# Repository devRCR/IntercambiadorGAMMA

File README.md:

# IntercambiadorGAMMA
Distributed control system for a Gamma heat exchanger using microcontrollers. Includes a Master Node for user input and two Slave Nodes for spindle and wheel control. Nodes communicate via serial protocol with modular Arduino-based C++ code for synchronized and reliable automation.

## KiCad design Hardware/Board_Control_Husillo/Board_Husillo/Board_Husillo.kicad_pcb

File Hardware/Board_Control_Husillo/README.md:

# Husillo Board – Intercambiador Gamma

Este documento describe la placa electrónica utilizada para el control del **módulo de husillo** en el sistema de automatización del intercambiador Gamma, desarrollado por el **Laboratorio de Desarrollo Electrónico – IPEN**.

## 📷 Diagrama de la Placa

## 🔧 Descripción Técnica

La placa está diseñada para:

- Controlar un **motor paso a paso** mediante señales `STEP` y `DIR`.
- Alimentar y conmutar un **relé de captura** para el sistema Marinelli.
- Leer múltiples **sensores de posición** (ópticos o magnéticos).
- Integrar un **buzzer** para notificación acústica.
- Interfaz directa con **Arduino Mega 2560** a través de conectores macho/hembra.
- Soporte de comunicación serial (TTL) para control distribuido.

## 🧩 Interfaces

| Señal          | Función                          |
|----------------|----------------------------------|
| `M_EN`         | Habilitación de motor            |
| `M_STEP`       | Pulso de avance                  |
| `M_DIR`        | Dirección de movimiento          |
| `RELAY`        | Activación del sistema Marinelli |
| `SENS_POS1-3`  | Sensores de posición del husillo |
| `SENS_MARx`    | Sensores de estado de Marinelli  |
| `BUZZER`       | Alarma sonora                    |
| `LCD`          | Salida para pantalla LCD 16x2    |

## 🛠️ Fabricación

- PCB de doble cara
- Conectores tipo Molex o bornes atornillables
- Compatible con montaje en riel DIN o chasis metálico

## 📄 Licencia

Este diseño se distribuye bajo **Creative Commons Atribución-NoComercial 4.0 Internacional (CC BY-NC 4.0)**. Su uso y modificación están permitidos únicamente para fines no comerciales, con la debida atribución a los autores.

## 👤 Autores

- O. Baltuano  
- R. Chan  
**Laboratorio de Desarrollo Electrónico – IPEN**

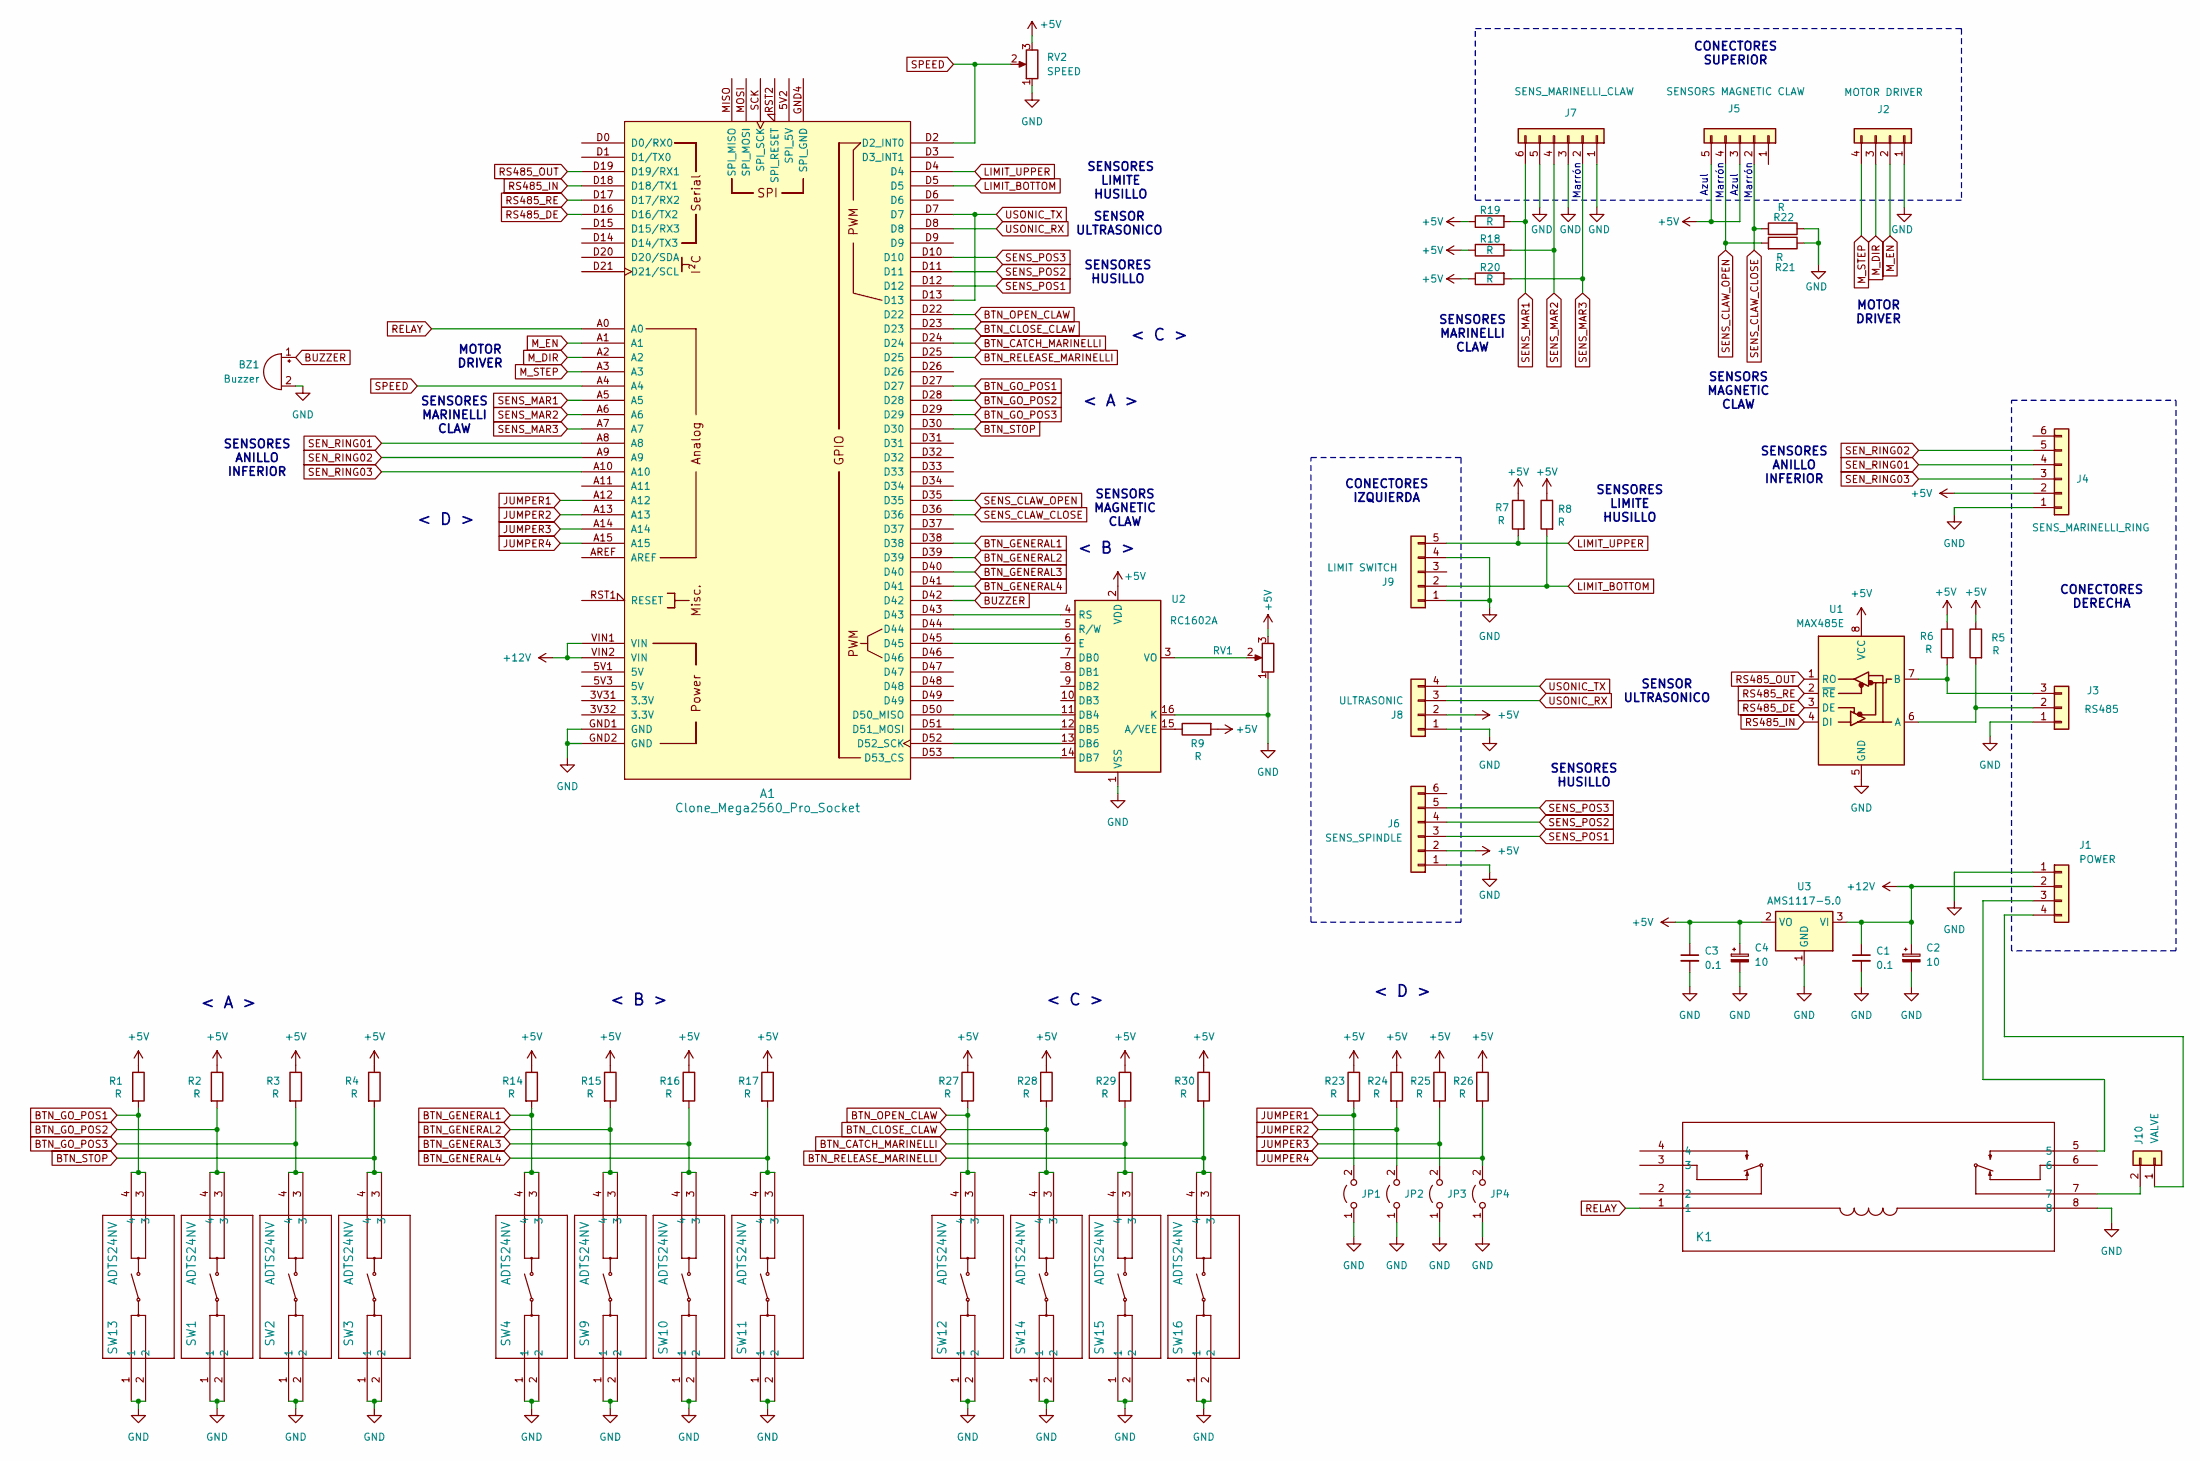
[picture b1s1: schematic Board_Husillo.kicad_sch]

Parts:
A1: Clone_Mega2560_Pro_Socket
BZ1: Buzzer; Buzzer_12x9.5RM7.6
C1, C3: 0.1; C_0805_2012Metric
C2, C4: 10; CP_Radial_D5.0mm_P2.50mm
J1: POWER; Molex_KK-396_5273-04A_1x04_P3.96mm_Vertical
J2: MOTOR DRIVER; PinHeader_1x04_P2.54mm_Vertical
J3: RS485; PinHeader_1x03_P2.54mm_Vertical
J4: SENS_MARINELLI_RING; PinHeader_1x06_P2.54mm_Vertical
J5: SENSORS MAGNETIC CLAW; PinHeader_1x05_P2.54mm_Vertical
J6: SENS_SPINDLE; PinHeader_1x06_P2.54mm_Vertical
J7: SENS_MARINELLI_CLAW; PinHeader_1x06_P2.54mm_Vertical
J8: ULTRASONIC; PinHeader_1x04_P2.54mm_Vertical
J9: LIMIT SWITCH; PinHeader_1x05_P2.54mm_Vertical
J10: VALVE; Molex_KK-396_A-41791-0002_1x02_P3.96mm_Vertical
JP1, JP2, JP3, JP4: Jumper_2_Open; PinHeader_1x02_P2.54mm_Vertical
K1: HRS2H-S DC12V; HRS2H-S DC9V_MTC
R1, R2, R3, R4, R9, R14, R15, R16, R17, R27, R28, R29, R30: R; R_Axial_DIN0207_L6.3mm_D2.5mm_P7.62mm_Horizontal
R5, R6, R7, R8, R18, R19, R20, R21, R22, R23, R24, R25, R26: R; R_0805_2012Metric
RV1: CONTRASTE; Potentiometer_ACP_CA9-V10_Vertical
RV2: SPEED; Potentiometer_ACP_CA9-V10_Vertical
SW1, SW2, SW3, SW4, SW9, SW10, SW11, SW12, SW13, SW14, SW15, SW16: ADTS24NV; ADTS24&asterisk_V_APM
U1: MAX485E; SOIC-8_5.23x5.23mm_P1.27mm
U2: RC1602A; WC1602A
U3: AMS1117-5.0; SOT-223-3_TabPin2

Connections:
+5V: C3.1, C4.1, J4.2, J5.3, J5.5, J6.2, J8.2, R1.1, R2.1, R3.1, R4.1, R5.1, R6.1, R7.1, R8.1, R9.2, R14.1, R15.1, R16.1, R17.1, R18.1, R19.1, R20.1, R23.1, R24.1, R25.1, R26.1, R27.1, R28.1, R29.1, R30.1, RV1.3, RV2.3, U1.8 (VCC), U2.2 (VDD), U3.2 (VO)
+12V: A1.VIN1 (VIN), A1.VIN2 (VIN), C1.1, C2.1, J1.2, U3.3 (VI)
BTN_CATCH_MARINELLI: A1.D24, R29.2, SW15.3, SW15.4
BTN_CLOSE_CLAW: A1.D23, R28.2, SW14.3, SW14.4
BTN_GENERAL1: A1.D38, R14.2, SW4.3, SW4.4
BTN_GENERAL2: A1.D39, R15.2, SW9.3, SW9.4
BTN_GENERAL3: A1.D40, R16.2, SW10.3, SW10.4
BTN_GENERAL4: A1.D41, R17.2, SW11.3, SW11.4
BTN_GO_POS1: A1.D27, R1.2, SW13.3, SW13.4
BTN_GO_POS2: A1.D28, R2.2, SW1.3, SW1.4
BTN_GO_POS3: A1.D29, R3.2, SW2.3, SW2.4
BTN_OPEN_CLAW: A1.D22, R27.2, SW12.3, SW12.4
BTN_RELEASE_MARINELLI: A1.D25, R30.2, SW16.3, SW16.4
BTN_STOP: A1.D30, R4.2, SW3.3, SW3.4
BUZZER: A1.D42, BZ1.1 (+)
GND: A1.GND1 (GND), A1.GND2 (GND), BZ1.2 (-), C1.2, C2.2, C3.2, C4.2, J1.1, J2.1, J3.1, J4.1, J6.1, J7.1, J7.3, J7.5, J8.1, J9.1, J9.4, JP1.1 (A), JP2.1 (A), JP3.1 (A), JP4.1 (A), K1.8, R21.1, R22.1, RV1.1, RV2.1, SW1.1, SW1.2, SW2.1, SW2.2, SW3.1, SW3.2, SW4.1, SW4.2, SW9.1, SW9.2, SW10.1, SW10.2, SW11.1, SW11.2, SW12.1, SW12.2, SW13.1, SW13.2, SW14.1, SW14.2, SW15.1, SW15.2, SW16.1, SW16.2, U1.5 (GND), U2.1 (VSS), U2.16 (K), U3.1 (GND)
JUMPER1: A1.A12, JP1.2 (B), R23.2
JUMPER2: A1.A13, JP2.2 (B), R24.2
JUMPER3: A1.A14, JP3.2 (B), R25.2
JUMPER4: A1.A15, JP4.2 (B), R26.2
LIMIT_BOTTOM: A1.D5, J9.2, R8.2
LIMIT_UPPER: A1.D4, J9.5, R7.2
M_DIR: A1.A2, J2.3
M_EN: A1.A1, J2.2
M_STEP: A1.A3, J2.4
unnamed: A1.A4, A1.D2 (D2_INT0), RV2.2
unnamed: A1.D50 (D50_MISO), U2.11 (DB4)
unnamed: A1.D51 (D51_MOSI), U2.12 (DB5)
unnamed: A1.D52 (D52_SCK), U2.13 (DB6)
unnamed: A1.D53 (D53_CS), U2.14 (DB7)
unnamed: J1.3, K1.5
unnamed: J1.4, J10.1
unnamed: J3.2, R5.2, U1.6 (A)
unnamed: J3.3, R6.2, U1.7 (B)
unnamed: J10.2, K1.7
unnamed: R9.1, U2.15 (A/VEE)
unnamed: A1.D45, U2.6 (E)
unnamed: A1.D43, U2.4 (RS)
unnamed: A1.D44, U2.5 (R/W)
unnamed: RV1.2, U2.3 (VO)
RELAY: A1.A0, K1.1
RS485_DE: A1.D16 (D16/TX2), U1.3 (DE)
RS485_IN: A1.D18 (D18/TX1), U1.4 (DI)
RS485_OUT: A1.D19 (D19/RX1), U1.1 (RO)
RS485_RE: A1.D17 (D17/RX2), U1.2 (~RE)
SENS_CLAW_CLOSE: A1.D36, J5.2, R22.2
SENS_CLAW_OPEN: A1.D35, J5.4, R21.2
SENS_MAR1: A1.A5, J7.6, R19.2
SENS_MAR2: A1.A6, J7.4, R18.2
SENS_MAR3: A1.A7, J7.2, R20.2
SENS_POS1: A1.D12, J6.3
SENS_POS2: A1.D11, J6.4
SENS_POS3: A1.D10, J6.5
SEN_RING01: A1.A8, J4.4
SEN_RING02: A1.A9, J4.5
SEN_RING03: A1.A10, J4.3
USONIC_RX: A1.D8, J8.3
USONIC_TX: A1.D7, A1.D13, J8.4

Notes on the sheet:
Marrón
SENSORS MAGNETIC CLAW
< D >
SENSORES LIMITE HUSILLO
CONECTORES SUPERIOR
SENSORES MARINELLI CLAW
CONECTORES DERECHA
CONECTORES IZQUIERDA
MOTOR DRIVER
< A >
< C >
Azul
SENSOR ULTRASONICO
SENSORES HUSILLO
SENSORES ANILLO INFERIOR
< B >

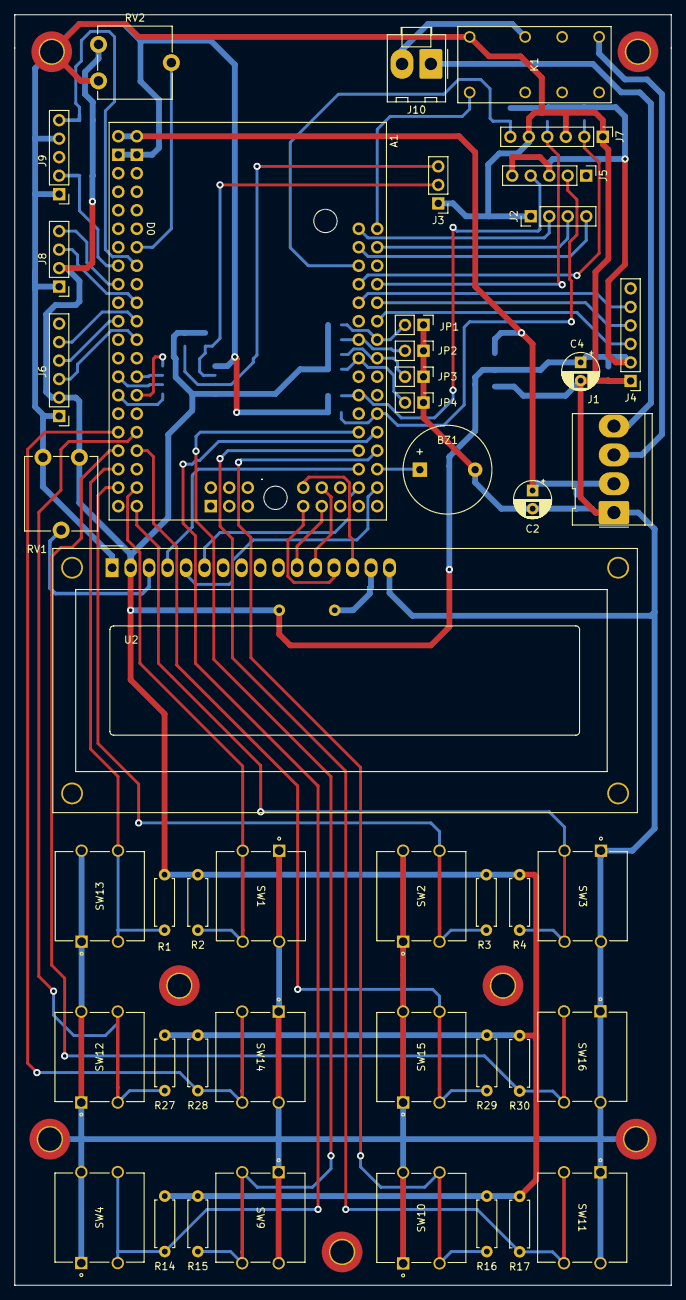
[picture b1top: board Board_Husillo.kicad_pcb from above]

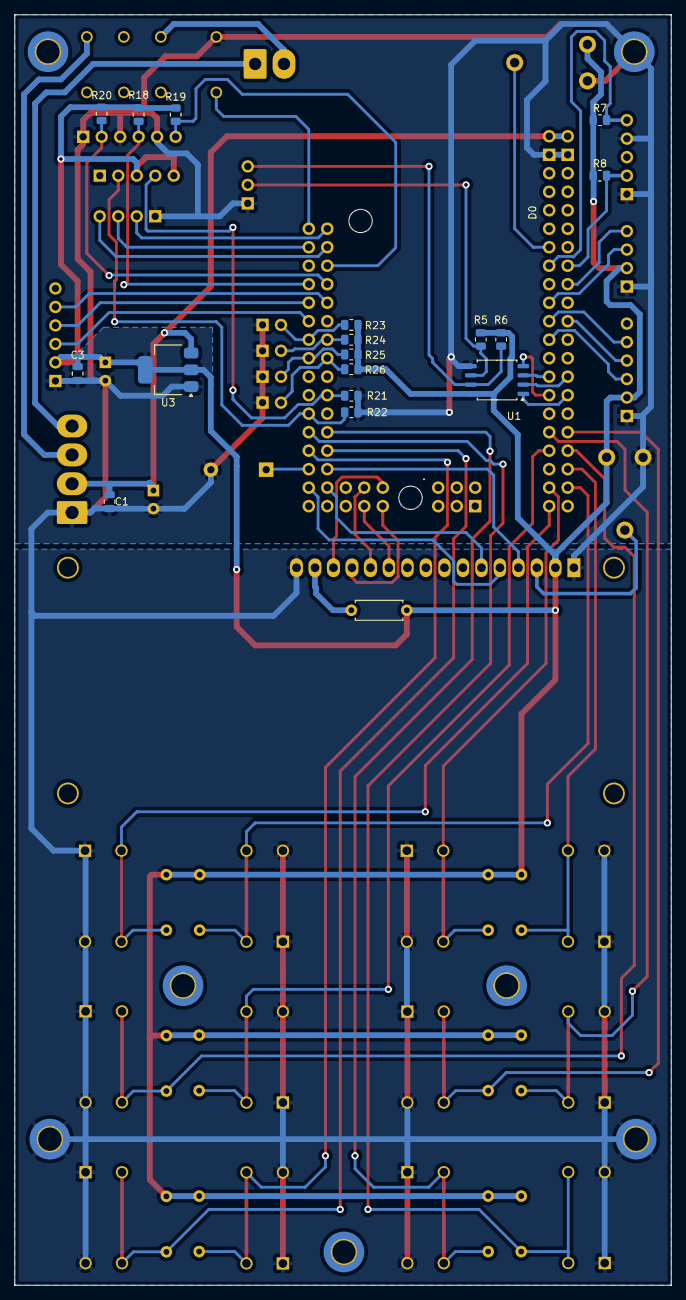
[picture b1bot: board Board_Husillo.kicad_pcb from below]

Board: 2 copper layers, 90.2 x 174.5 mm, 64 parts (18 on the bottom side), 58 nets.

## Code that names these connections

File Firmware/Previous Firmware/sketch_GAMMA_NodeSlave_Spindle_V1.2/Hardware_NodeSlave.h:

// PINES CONTROL
// PUERTO SERIAL 1
#define     RS485_RE  17
#define     RS485_DE  16

// PINES PANTALLA LCD
#define     LCD_RS    43
#define     LCD_RW    44
#define     LCD_EN    45
#define     LCD_D4    50
#define     LCD_D5    51
#define     LCD_D6    52
#define     LCD_D7    53

// PINS MOTOR HUSILLO
#define     M_EN      A1
#define     M_DIR     A2
#define     M_STEP    A3
#define     DirRight  HIGH
#define     DirLeft   LOW 

// VELOCIDAD
#define SENS_SPEED    A4

// PIN CONTROL RELAY
#define     RELAY     A0

// PIN CONTROL BUZZER
#define     BUZZER    42

// SENSORES DETECTOR MARINELLI GARRA
#define   SENS_MAR1   A5
#define   SENS_MAR2   A6
#define   SENS_MAR3   A7

// ANILLO INFERIOR DE SENSORES
#define   SENS_RING01   A8
#define   SENS_RING02   A9
#define   SENS_RING03   A10

// SENSORES DE HUSILLO
#define   SENS_POS1   12
#define   SENS_POS2   11
#define   SENS_POS3   10

// SENSORES MAGNETICOS GARRA
#define   SENS_CLAW_OPEN    35
#define   SENS_CLAW_CLOSE   36

// BOTONES DE MOVIMIENTO DEL HUSILLO
#define   BTN_GO_POS1     27
#define   BTN_GO_POS2     28
#define   BTN_GO_POS3     29
#define   BTN_STOP        30

// BOTONES DE CONTROL GARRA
#define   BTN_MARI_CATCH_TOP      22
#define   BTN_MARI_RELEASE_TOP    23
#define   BTN_MARI_CATCH_BOTTOM   24
#define   BTN_MARI_RELEASE_BOTTOM 25

// BOTONES GENERALES
#define   BTN_GENERAL1    38
#define   BTN_GENERAL2    39
#define   BTN_GENERAL3    40
#define   BTN_GENERAL4    41

// JUMPERS
#define   JUMPER1     A12
#define   JUMPER2     A12
#define   JUMPER3     A12
#define   JUMPER4     A12

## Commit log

2025-03-18 Initial commit: add GAMMA control system files
2025-03-31 version firmware changed
2025-03-31 GAMMA NodeMaster Buttons created
2025-04-01 firmware folders created
2025-04-01 readme added
2025-04-01 folders reorganized
2025-04-01 husillo board files created
2025-04-01 readme created
2025-05-16 gripper image
2025-05-19 SoC w/ Design Patterns Implemented
2025-05-19 SAMPLE_PREV instead SAMPLE_CYCLE
2025-05-19 print menssage updated
2025-05-19 Implement numeric validation
2025-05-19 WheelComm.cpp update
2025-05-19 Validate numeric command values from GUI
2025-05-19 Add missing initGUI function implementation
2025-05-19 Initial modular code for GripperNode
2025-05-19 Update MasterNode for GripperNode support
2025-05-19 Include Arduino header in main.cpp
2025-05-19 Match GripperComm format to WheelComm
2025-05-19 Fix UART startup timing in master
2025-05-19 Send startup T0 commands to flush buffers
2025-05-20 Add physical button pin definitions only
2025-05-20 Flush all serial input buffers at startup
2025-05-20 Refactor button declarations using macro
2025-05-20 GripperNode message updated
2025-05-20 message updated
2025-05-20 Verify node communication on startup
2025-05-20 print mode changed
2025-05-20 Implement T0 command in WheelNode for status check
2025-05-20 Clean and document WheelNode command executor
2025-05-20 Enable both GUI and button control in master
2025-05-20 Fix enum scope for button destination
2025-05-20 Rename SAMPLE_CYCLE to SAMPLE_PREV
2025-05-21 Verify ACK validity before confirming node communication
2025-05-23 Integrate modular control for Wheel Node and Master Node
2025-05-23 Confirm ShieldControl ACK send with debug feedback
2025-05-23 Finalize SampleControl with FSM and serial ACK feedback
2025-05-26 timeout updated
2025-05-26 command list added
2025-05-26 big changes
2025-05-26 list of comands
2025-05-26 Speeds config
2025-05-27 security logic changed
2025-05-28 Protocol and States defined
2025-05-30 Gripper node implemented
2025-05-30 CommandExecutor functions used
